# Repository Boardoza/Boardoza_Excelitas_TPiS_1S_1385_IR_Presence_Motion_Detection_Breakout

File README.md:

# Boardoza Excelitas TPiS 1S 1385 High-Sensitivity Presence Sensor Breakout Board

The **Boardoza Excelitas TPiS 1S 1385** is a compact and ultra-low-power **infrared presence and motion detection breakout board** based on the **Excelitas TPiS 1S 1385** thermopile sensor. Designed for **non-contact presence sensing**, this module integrates a high-sensitivity thermopile with a **120° field of view**, ideal for motion-triggered lighting, smart occupancy detection, and thermal monitoring in energy-efficient IoT systems.

It features an **I²C interface** (default address: 0x0C), integrated digital signal processing, and a dedicated **interrupt pin** for presence, movement, and temperature threshold events. With just **15µA of typical current draw**, the TPiS 1S 1385 is an ideal solution for battery-powered and energy-sensitive applications.

## [Click here to purchase!](https://www.ozdisan.com/maker-ve-iot-urunleri/boardoza/boardoza-modulleri/BOARDOZA-TPIS1385/1473945)

|Front Side|Back Side|
|:---:|:---:|
| | |

---

## Key Features

- **High-Sensitivity Infrared Thermopile:** Designed for non-contact presence, motion, and temperature detection.
- **120° Field of View:** Wide-area sensing coverage for smart automation and ambient detection.
- **Digital Signal Processing:** Onboard 50 µW processing engine filters noise and enhances reliability.
- **Low Power Consumption:** Ultra-low 15µA supply current for long-lasting operation.
- **I²C Interface:** Communicates easily with MCUs (default address: 0x0C).
- **Interrupt Functionality:** Dedicated interrupt pin triggers alerts for configurable motion and thermal thresholds.

---

## Technical Specifications

**Model:** Excelitas TPiS 1S 1385  
**Input Voltage:** 3.3V – 5V  
**Supply Current:** 15µA (typical)  
**Functions:** High-Sensitivity Presence and Motion Sensor  
**Communication:** I²C (Default Address: 0x0C)  
**Field of View:** 120°  
**Operating Temperature:** -20°C ~ +85°C  
**Board Dimensions:** 20mm x 20mm  

---

## **Board Pinout**

| Pin Number | Pin Name | Description                |
|:----------:|:--------:|----------------------------|
| 1          | VCC      | Positive Power Supply (3.3V–5V) |
| 2          | SCL      | I²C Serial Clock Input      |
| 3          | SDA      | I²C Serial Data             |
| 4          | INT      | Interrupt Output            |
| 5          | GND      | Ground                      |

---

## Board Dimensions

---

## Step Files

[Boardoza TPiS_1S_1385.step](./assets/TPiS%201S%201385%20Step.step)

---

## Datasheet

[TPiS_1S_1385 Datasheet.pdf](.)

---

## Version History

- V1.0.0 - Initial Release

---

## Support

- If you have any questions or need support, please contact <support@boardoza.com>

---

## License

Shield: [![CC BY-SA 4.0][cc-by-sa-shield]][cc-by-sa]

This work is licensed under a [Creative Commons Attribution-ShareAlike 4.0 International License][cc-by-sa].

[![CC BY-SA 4.0][cc-by-sa-image]][cc-by-sa]

[cc-by-sa]: http://creativecommons.org/licenses/by-sa/4.0/
[cc-by-sa-image]: https://licensebuttons.net/l/by-sa/4.0/88x31.png
[cc-by-sa-shield]: https://img.shields.io/badge/License-CC%20BY--SA%204.0-lightgrey.svg

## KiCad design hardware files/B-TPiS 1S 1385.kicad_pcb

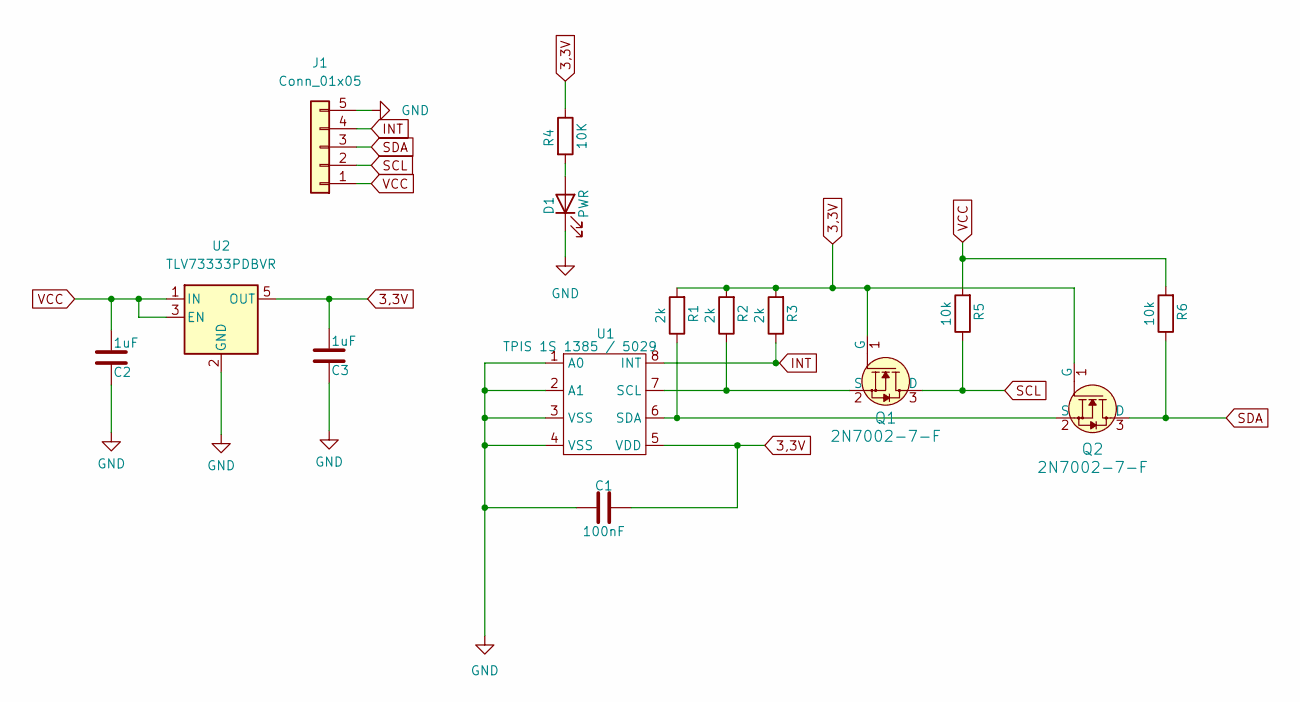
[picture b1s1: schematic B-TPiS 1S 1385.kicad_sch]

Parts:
C1: 100nF; C_0603_1608Metric; MPN CL10B104KB8NNNC
C2, C3: 1uF; C_0603_1608Metric; MPN CL10A105KO8NNNC
D1: PWR; LED_0603_1608Metric; MPN 19-213USRC/S259/TR8
J1: Conn_01x05; 2317-05S_1x05_P2.50mm_Vertical
Q1, Q2: 2N7002-7-F; SOT-23-3; MPN 2N7002_R1_00001
R1, R2, R3: 2k; R_0603_1608Metric; MPN 0603SAJ0202T5E
R4: 10K; R_0603_1608Metric; MPN 0603SAJ0103T5E
R5, R6: 10k; R_0603_1608Metric; MPN 0603SAJ0103T5E
U1: TPIS 1S 1385 / 5029; Temperature SensorSMD; MPN TPIS 1S 1385 / 5029
U2: TLV73333PDBVR; SOT-23-5; MPN TLV73333PDBVR

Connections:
3,3V: C1.2, C3.1, Q1.1 (G), Q2.1 (G), R1.2, R2.2, R3.2, R4.1, U1.5 (VDD), U2.5 (OUT)
GND: C1.1, C2.1, C3.2, D1.1 (K), J1.5, U1.1 (A0), U1.2 (A1), U1.3 (VSS), U1.4 (VSS), U2.2 (GND)
INT: J1.4, R3.1, U1.8 (INT)
unnamed: D1.2 (A), R4.2
unnamed: Q1.2 (S), R2.1, U1.7 (SCL)
unnamed: Q2.2 (S), R1.1, U1.6 (SDA)
SCL: J1.2, Q1.3 (D), R5.1
SDA: J1.3, Q2.3 (D), R6.1
VCC: C2.2, J1.1, R5.2, R6.2, U2.1 (IN), U2.3 (EN)

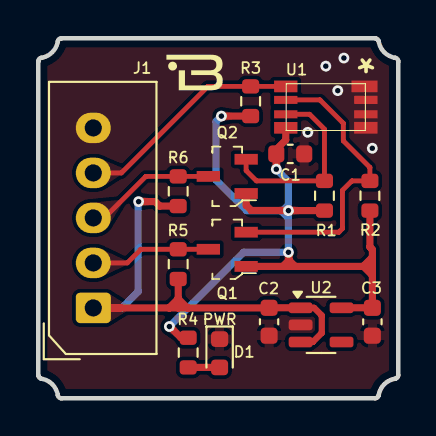
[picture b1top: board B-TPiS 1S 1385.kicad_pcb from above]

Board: 2 copper layers, 20.0 x 20.0 mm, 15 parts (0 on the bottom side), 9 nets.

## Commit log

2025-05-21 initial release for Excelitas TPiS 1S 1385 breakout board
2025-05-21 Add TPIS 1S 1385 library
